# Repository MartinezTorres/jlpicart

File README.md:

# JLPiCart - MSX Cartridge Based on RP2350B

JLPiCart is an experimental MSX cartridge design based on the RP2350B. This is a preliminary version with several known bugs, but early tests show promising results. We have ordered a small production run, and we are offering units to those interested in developing their own RP2350B firmware. If you'd like to obtain one, please contact me.

## Status
The firmware for the PCB is a work in progress. Some features are already functional, while others are still under development. Below is the current status of the key components:

| Feature              | Status                                        |
|----------------------|----------------------------------------------|
| RP2350B main CPU    | Hardware works and tested. Functional.       |
| Primary MSX slot    | Hardware works, code is there, works.        |
| Subslots            | Hardware works, code is there. Not working.  |
| VGA output          | Hardware works, code is there. Almost stable.|
| CRT output          | Hardware works, code is there. Almost stable.|
| TMS9918 emulation   | Hardware works, mode 2 support only. Almost stable. |
| WIFI and BT         | Communication with ESP32 achieved.           |
| E-INK interface     | Not tested.                                  |
| OLED screen         | Hardware works. Bitbanged I2C works.         |
| USB                 | Hardware works. Software is in early stages of development. |
| Battery overcharging| Still investigating hardware.                |

## Schematics and Images
Below are various images related to the JLPiCart hardware design:

### Schematic

### Top Assembly Drawing

### PCB Images
#### Front

#### Back

## Development
We are actively working on improving the firmware. Contributions and feedback are welcome. If you encounter any issues or have suggestions, feel free to reach out.

## Contact
For inquiries, development collaboration, or to request a unit, please contact me.

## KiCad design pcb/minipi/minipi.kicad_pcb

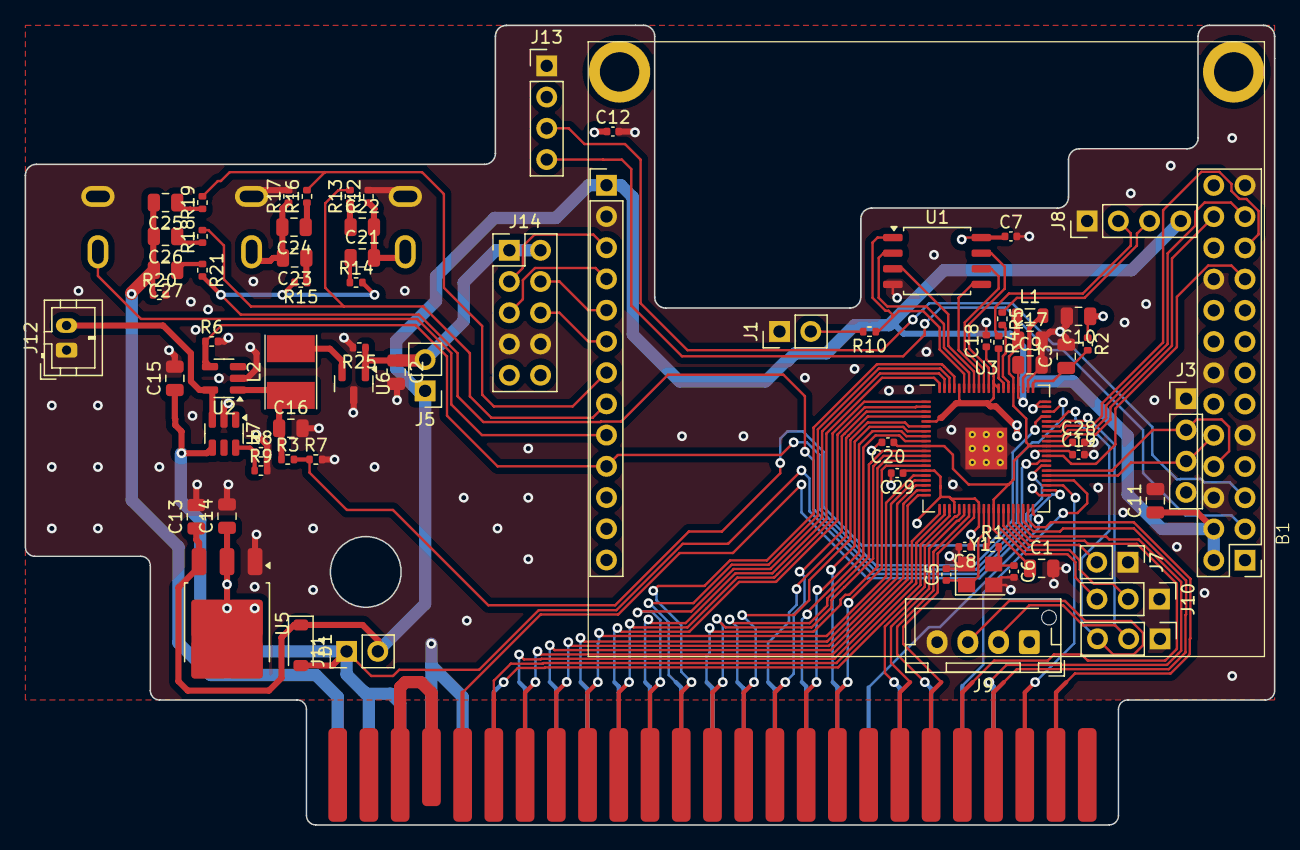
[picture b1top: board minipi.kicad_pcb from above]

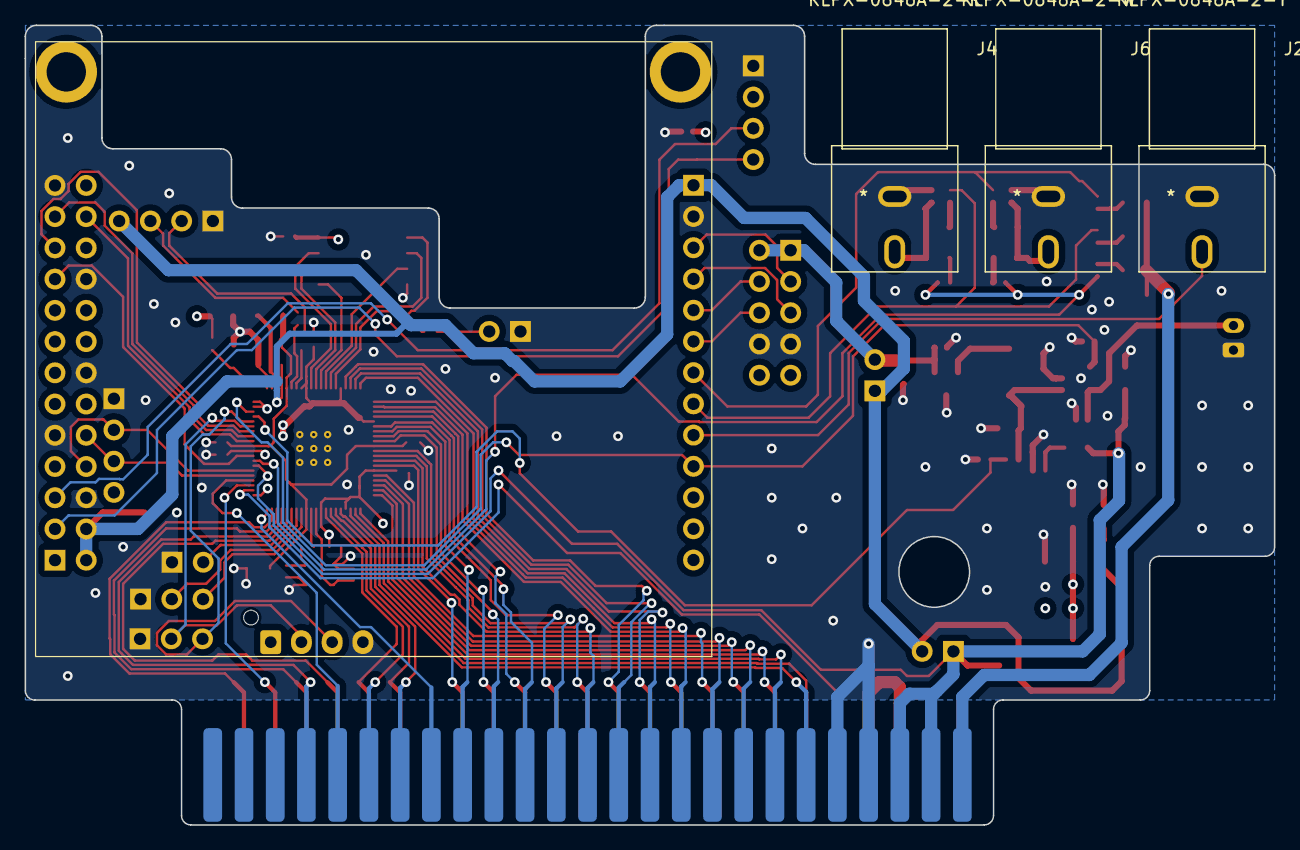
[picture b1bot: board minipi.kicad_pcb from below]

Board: 4 copper layers, 101.6 x 65.0 mm, 75 parts (3 on the bottom side), 96 nets.

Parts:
B1: Orange_PI_Zero_3; Orange Pi Zero 3
BUS1: MSX_SLOT_EDGE-CON; msx_cartridge_basic
C1, C2, C3, C9, C10, C11, C13, C14, C15, C16, C17, C21, C22, C23, C24, C25, C26, C27: 10u; C_0805_2012Metric
C5, C6: 15p; C_0402_1005Metric
C7, C8, C12, C18, C19, C20, C28, C29: 100nF; C_0402_1005Metric
D1: MBR0520; D_SOD-123
J1, J5, J7, J11: Conn_01x02; PinHeader_1x02_P2.54mm_Vertical
J2: KLPX-0848A-2-Y; KLPX-0848A-2-R
J3, J8, J13: Conn_01x04; PinHeader_1x04_P2.54mm_Vertical
J4: KLPX-0848A-2-R
J6: KLPX-0848A-2-W; KLPX-0848A-2-R
J9: Conn_01x04; JST_XH_B4B-XH-AM_1x04_P2.50mm_Vertical
J10: Conn_01x03; PinHeader_1x03_P2.54mm_Vertical
J12: Conn_01x02; JST_PH_B2B-PH-K_1x02_P2.00mm_Vertical
J14: Conn_02x05_Odd_Even; PinHeader_2x05_P2.54mm_Vertical
L1: 3.3u; L_0805_2012Metric
L2: 3.3u; L_Taiyo-Yuden_NR-40xx_HandSoldering
R1, R10: 1k; R_0402_1005Metric
R2, R4, R5: 27; R_0402_1005Metric
R3, R6, R7, R8, R9, R12, R13, R14, R15, R16, R17, R18, R19, R20, R21, R25: 10k; R_0402_1005Metric
U1: W25Q128JVS; SOIC-8_5.23x5.23mm_P1.27mm
U2: AP22804AW5; SOT-23-5
U3: RP2350_80QFN; RP2350-QFN-80-1EP_10x10_P0.4mm_EP3.4x3.4mm_ThermalVias
U5: AMS1117CD-3.3; TO-252-3_TabPin2
U6: TPS613222ADBZ; SOT-23
U7: TP4057; TSOT-23-6
Y1: ABM8-272-T3; Crystal_SMD_3225-4Pin_3.2x2.5mm

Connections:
1V1: C1.1, C17.1, C20.1, C28.1, L1.1, U3.10 (DVDD), U3.32 (DVDD), U3.51 (DVDD), U3.65 (VREG_FB)
3V3: B1.1 (VCC-3V3), B1.17 (VCC-3V3), C7.1, C8.1, C10.1, C12.1, C14.1, C18.1, C19.1, C29.1, J3.4, J13.2, R2.1, U1.8 (VCC), U3.5 (IOVDD), U3.15 (IOVDD), U3.24 (IOVDD), U3.29 (IOVDD), U3.41 (IOVDD), U3.50 (IOVDD), U3.59 (ADC_AVDD), U3.60 (IOVDD), U3.68 (USB_OTP_VDD), U3.69 (QSPI_IOVDD), U3.76 (IOVDD), U5.2 (VO)
5V: B1.2 (VCC-5V), B1.4 (VCC-5V), B1.E1 (VCC-5V), C9.1, C11.1, C13.1, D1.1 (K), J5.1, J8.4, J11.2, U3.64 (VREG_VIN), U5.3 (VI)
5V_BAT: C2.1, J5.2, J14.1, J14.2, R25.1, U6.1 (VOUT)
5V_IN: BUS1.45 (+5V), BUS1.47 (+5V), C15.1, D1.2 (A), J11.1, U3.47 (GPIO38), U7.4 (V_{CC})
/A0: BUS1.28 (A0), U3.77 (GPIO0)
/A1: BUS1.27 (A1), U3.78 (GPIO1)
/A2: BUS1.30 (A2), U3.79 (GPIO2)
/A3: BUS1.29 (A3), U3.80 (GPIO3)
/A4: BUS1.32 (A4), U3.1 (GPIO4)
/A5: BUS1.31 (A5), U3.2 (GPIO5)
/A6: BUS1.22 (A6), U3.3 (GPIO6)
/A7: BUS1.21 (A7), U3.4 (GPIO7)
/A8: BUS1.24 (A8), U3.6 (GPIO8)
/A9: BUS1.17 (A9), U3.7 (GPIO9)
/A10: BUS1.20 (A10), U3.8 (GPIO10)
/A11: BUS1.19 (A11), U3.9 (GPIO11)
/A12: BUS1.23 (A12), U3.11 (GPIO12)
/A13: BUS1.26 (A13), U3.12 (GPIO13)
/A14: BUS1.25 (A14), U3.13 (GPIO14)
/A15: BUS1.18 (A15), U3.14 (GPIO15)
/D0: BUS1.34 (D0), U3.16 (GPIO16)
/D1: BUS1.33 (D1), U3.17 (GPIO17)
/D2: BUS1.36 (D2~), U3.18 (GPIO18)
/D3: BUS1.35 (D3), U3.19 (GPIO19)
/D4: BUS1.38 (D4), U3.20 (GPIO20)
/D5: BUS1.37 (D5), U3.21 (GPIO21)
/D6: BUS1.40 (D6), U3.22 (GPIO22)
/D7: BUS1.39 (D7), U3.23 (GPIO23)
/EN_5V: B1.E10 (PC1), R6.1, U2.4 (EN), U3.58 (GPIO47_ADC7)
/LINEOUT_LL: B1.E7 (LINEOUT-LL), R16.2, R19.2
/LINEOUT_LR: B1.E8 (LINEOUT-LR), R13.2, R18.2
/LINEOUT_RP: R14.2, R15.2, R21.2, U3.48 (GPIO39)
/QSPI_SCLK: U1.6 (CLK), U3.71 (QSPI_SCLK)
/QSPI_SD0: U1.5 (DI(IO0)), U3.72 (QSPI_SD0)
/QSPI_SD1: U1.2 (DO(IO1)), U3.74 (QSPI_SD1)
/QSPI_SD2: U1.3 (IO2), U3.73 (QSPI_SD2)
/QSPI_SD3: U1.7 (IO3), U3.70 (QSPI_SD3)
/QSPI_SS: R10.1, U1.1 (~CS), U3.75 (QSPI_SS)
/RUN: J7.2, U3.35 (RUN)
/SCK: B1.5 (I2C3-SCK), J13.3
/SDA: B1.3 (I2C3-SDA), J13.4
/SND: BUS1.49 (SOUNDOUT), C25.2, C26.2, C27.2, R20.1
/SPI0_CLK: B1.23 (SPI1-CLK), U3.53 (GPIO42_ADC2)
/SPI0_CS: B1.24 (SPI1-CS), U3.52 (GPIO41_ADC1)
/SPI0_MISO: B1.21 (SPI1-MISO), U3.54 (GPIO43_ADC3)
/SPI0_MOSI: B1.19 (SPI1-MOSI), U3.49 (GPIO40_ADC0)
/SW1: BUS1.44 (SW1), BUS1.46 (SW2)
/SWCLK: J10.3, U3.33 (SWCLK)
/SWD: J10.2, U3.34 (SWD)
/SYS_CLK: BUS1.42 (CLOCK), U3.42 (GPIO33)
/TV_OUT: B1.E9 (TV-OUT), J2.1 (In)
/UART0_RP_2_Z: B1.RX, J9.2, U3.55 (GPIO44_ADC4)
/UART0_Z_2_RP: B1.TX, J9.3, U3.56 (GPIO45_ADC5)
/UART1_RP_2_Z: B1.10 (UART5-RX), J3.3, U3.45 (GPIO36)
/UART1_Z_2_RP: B1.8 (UART5-TX), J3.2, U3.46 (GPIO37)
/USB2_DM: B1.E3 (USB2-DM), J14.3
/USB2_DP: B1.E4 (USB2-DP), J14.5
/USB3_DM: B1.E5 (USB3-DM), J14.4
/USB3_DP: B1.E6 (USB3-DP), J14.6
/USB_D+: J8.2, R4.1
/USB_D-: J8.3, R5.1
/V_LIPO_HALF: R3.2, R7.1, U3.57 (GPIO46_ADC6)
/~BUSDIR: BUS1.10 (~BUSDIR), U3.36 (GPIO28)
/~INT: BUS1.8 (~INT), U3.38 (GPIO30)
/~IORQ: BUS1.11 (~IORQ), U3.27 (GPIO26)
/~M1: BUS1.9 (~M1), U3.44 (GPIO35)
/~MERQ: BUS1.12 (~MERQ), U3.28 (GPIO27)
/~RD: BUS1.14 (~RD), U3.26 (GPIO25)
/~RESET: BUS1.15 (~RESET), U3.40 (GPIO32)
/~RFSH: BUS1.6 (~RFSH), U3.43 (GPIO34)
/~SLTSL: BUS1.4 (~SLTSL), U3.39 (GPIO31)
/~USB_BOOT: J1.2, R10.2
/~WAIT: BUS1.7 (~WAIT), U3.37 (GPIO29)
/~WR: BUS1.13 (~WR), U3.25 (GPIO24)
AVDD_3V3: C3.1, R2.2, U3.61 (VREG_AVDD)
GND: B1.6 (GND), B1.9 (GND), B1.14 (GND), B1.20 (GND), B1.25 (GND), B1.E2 (GND), B1.GND, BUS1.41 (GND), BUS1.43 (GND), C1.2, C2.2, C3.2, C5.2, C6.2, C7.2, C8.2, C9.2, C10.2, C11.2, C12.2, C13.2, C14.2, C15.2, C16.2, C17.2, C18.2, C19.2, C20.2, C28.2, C29.2, J1.1, J2.2 (Ext), J3.1, J4.2 (Ext), J6.2 (Ext), J7.1, J8.1, J9.4, J10.1, J12.1, J13.1, J14.7, J14.8, R6.2, R7.2, R8.2, R9.2, R12.2, R17.2, R20.2, R25.2, U1.4 (GND), U2.2 (GND), U3.62 (VREG_PGND), U3.81 (GND), U5.1 (GND), U6.3 (GND), U7.2 (GND), Y1.2, Y1.4
unnamed: C6.1, R1.2, Y1.3
unnamed: C21.1, R14.1
unnamed: C22.1, R13.1
unnamed: C23.1, R15.1
unnamed: C24.1, R16.1
unnamed: C25.1, R19.1
unnamed: C26.1, R18.1
unnamed: C27.1, R21.1
unnamed: C21.2, C22.2, J4.1 (In), R12.1
unnamed: C23.2, C24.2, J6.1 (In), R17.1
unnamed: C16.1, L2.1, R3.1, U2.1 (OUT)
unnamed: R5.2, U3.66 (USB_DM)
unnamed: R4.2, U3.67 (USB_DP)
unnamed: L1.2, U3.63 (VREG_LX)
unnamed: C5.1, U3.30 (XIN), Y1.1
unnamed: R1.1, U3.31 (XOUT)
unnamed: L2.2, U6.2 (SW)
unnamed: R8.1, R9.1, U7.6 (PROG)
V_LIPO: J12.2, U2.5 (IN), U7.3 (BAT)

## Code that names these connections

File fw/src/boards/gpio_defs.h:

#pragma once
// gpio_defs.h — GPIO pin and bit constants for jlpicart_board (RP2350B).
//
// Describes the physical wiring between the RP2350B and the MSX cartridge slot.
// No SDK includes — pure constants safe to use in host tests and bus.cc alike.

#include <cstdint>

// GPIO number → RP2350 GPIO index (0-based).
enum PinMapping : int {
    GPIO_A0  = 0,  GPIO_A1  = 1,  GPIO_A2  = 2,  GPIO_A3  = 3,
    GPIO_A4  = 4,  GPIO_A5  = 5,  GPIO_A6  = 6,  GPIO_A7  = 7,
    GPIO_A8  = 8,  GPIO_A9  = 9,  GPIO_A10 = 10, GPIO_A11 = 11,
    GPIO_A12 = 12, GPIO_A13 = 13, GPIO_A14 = 14, GPIO_A15 = 15,

    GPIO_D0     = 16, GPIO_D1 = 17, GPIO_D2 = 18, GPIO_D3 = 19,
    GPIO_D4     = 20, GPIO_D5 = 21, GPIO_D6 = 22, GPIO_D7 = 23,

    GPIO_WR     = 24,
    GPIO_IORQ   = 25,
    GPIO_MERQ   = 26,
    GPIO_RD     = 27,
    GPIO_BUSDIR = 28,
    GPIO_INT    = 29,
    GPIO_WAIT   = 30,
    GPIO_SLTSL  = 31,

    // GPIOs 32-47 — accessed via sio_hw->gpio_hi_in / gpio_hi_out on RP2350.
    GPIO64_CLK     = 32,
    GPIO64_SND     = 33,
    GPIO64_RESET   = 34,
    GPIO64_M1      = 35,
    GPIO64_RFSH    = 36,
    GPIO64_OLEDSDA = 37,
    GPIO64_OLEDSCK = 38,
    GPIO64_V_VSYNC = 39,
    GPIO64_V_HSYNC = 40,
    GPIO64_V_BLUE  = 41,
    GPIO64_V_GREEN = 42,
    GPIO64_V_RED   = 43,
    GPIO64_UART_TX = 44,
    GPIO64_UART_RX = 45,
    GPIO64_VUSB_EN = 46,
    GPIO64_BATSENS = 47,
};

// Single 32-bit bitmask for GPIOs 0–31 (sio_hw->gpio_in / gpio_out / gpio_oe).
enum PinBitMapping : uint32_t {
    BIT_A0  = 1U << 0,  BIT_A1  = 1U << 1,  BIT_A2  = 1U << 2,  BIT_A3  = 1U << 3,
    BIT_A4  = 1U << 4,  BIT_A5  = 1U << 5,  BIT_A6  = 1U << 6,  BIT_A7  = 1U << 7,
    BIT_A8  = 1U << 8,  BIT_A9  = 1U << 9,  BIT_A10 = 1U << 10, BIT_A11 = 1U << 11,
    BIT_A12 = 1U << 12, BIT_A13 = 1U << 13, BIT_A14 = 1U << 14, BIT_A15 = 1U << 15,

    BIT_D0     = 1U << 16, BIT_D1 = 1U << 17, BIT_D2 = 1U << 18, BIT_D3 = 1U << 19,
    BIT_D4     = 1U << 20, BIT_D5 = 1U << 21, BIT_D6 = 1U << 22, BIT_D7 = 1U << 23,

    BIT_WR     = 1U << 24,
    BIT_IORQ   = 1U << 25,
    BIT_MERQ   = 1U << 26,
    BIT_RD     = 1U << 27,
    BIT_BUSDIR = 1U << 28,
    BIT_INT    = 1U << 29,
    BIT_WAIT   = 1U << 30,
    BIT_SLTSL  = 1U << 31,
};

// High-word bitmask for GPIOs 32–63 (sio_hw->gpio_hi_in on RP2350).
// BIT64_X_HI is bit (GPIO64_X - 32) of the high register.
enum PinBitMappingHi : uint32_t {
    BIT64_CLK_HI     = 1U << (GPIO64_CLK     - 32),  // bit 0
    BIT64_SND_HI     = 1U << (GPIO64_SND     - 32),  // bit 1
    BIT64_RESET_HI   = 1U << (GPIO64_RESET   - 32),  // bit 2
    BIT64_M1_HI      = 1U << (GPIO64_M1      - 32),  // bit 3
    BIT64_RFSH_HI    = 1U << (GPIO64_RFSH    - 32),  // bit 4
    BIT64_OLEDSDA_HI = 1U << (GPIO64_OLEDSDA - 32),  // bit 5
    BIT64_OLEDSCK_HI = 1U << (GPIO64_OLEDSCK - 32),  // bit 6
};

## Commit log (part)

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2024-09-15 firsts tests with pio
2025-02-11 Vga works
2025-03-03 lots of changes
2025-03-04 mini demo for nijmegen
2025-03-21 half-way rework, adding serialization
2025-12-01 huge mess...
2026-03-03 expand and restructure requirements document
    - Add section 3: Use Cases with nine named scenarios
    - Restructure section 5 (System Architecture) and section 6 (Requirements)
    - Split device emulation into ROM Payload Properties, Peripheral Devices,
    and remove SymbOS to Use Cases as a named compatibility target
    - Add Runtime Behavior as its own section, separate from Menu
    - Clean Menu section to focus only on the menu itself
2026-03-05 gitignore esp32-at.bin (large binary, not tracked)
2026-03-08 rename spec_v22.md → spec.md, bootstrapping_v8.md → bootstrapping.md
    Use canonical names as specified in Appendix B of the spec.
2026-03-09 stage 2: add fetch_sdcc step to CI build job
2026-03-09 complete stage 3 test coverage per bootstrapping checklist
    Add missing test cases listed in bootstrapping.md §3.6 and §3.10:
    §3.6 Policy verification:
    - test_policy_verify_sealed_one_bit_mutation_fails: flip one bit in flags,
    HMAC must reject it
    - test_policy_verify_sealed_wrong_key_fails: HMAC computed with a different
    key is rejected even if structurally valid
2026-03-09 stage 4: fix ring_push_msg wrap+full bug and clean up smells
    ring_push_msg free-space check was wrong when wrapping is needed.
    When frame_len > to_end, the [head, size) bytes are permanently wasted
    by the wrap marker; space consumed = to_end + frame_len, not frame_len.
    With ring_size=512 and max_frame=256 this was reachable: e.g. head=300,
    tail=4, frame_len=256 would pass the old check and overwrite unread
    consumer data at positions [4, 255]. Fixed by computing:
2026-03-09 stage 5: fix three spec compliance bugs in Z80 menu stub
    1. Joystick encoding inverted (MUST violation, spec §8 InputSnapshot):
    joy1/joy2 bits are active-low (0=pressed, 1=released) per spec, matching
    kbd_rows convention. Previous code started at 0 and set bits when active
    (active-high). Fixed: start at 0xFF (all released), clear bits on press.
    Trigger logic was also inverted (tested trig == 0 instead of trig != 0).
    2. PUT_TEXT: no clipping (MUST violation, spec §8):
2026-03-09 stage 6: fix bugs and clean up from deep analysis
    - Add STORAGE_NOT_FOUND (0x0303) DiagCode; use it in KvStore::get()
    instead of STORAGE_CORRUPT, which had the wrong semantics
    - Fix KvStore::init() tombstone logic: skip slot allocation entirely
    when a tombstone is encountered for a key not in the index
    - Parameterise storage_check_health() with explicit kv/log offsets
    instead of hardcoding flash layout constants; this makes it testable
2026-03-10 stage 7: Collections v1 — manifest, install engine, receipts, host tests
    Add the collection format, JSON manifest parser, atomic USB install engine,
    and install receipt logging. All 16 host tests pass (11/11 test targets).
    - src/content/collection_format.h: CollectionRecord (357B packed), bundle
    file constants, KV key/state constants, BundleSigEnvelope
    - src/content/manifest.h: CollectionManifest + PayloadEntry structs
    - src/content/manifest_parser.{h,cc}: minimal recursive-descent JSON parser
2026-03-10 stage 7: second audit — append_log guard, scan_records refactor, doc fixes
    - append_log: reject ALOG_TYPE_ERASED (0xFF) in append() — writing the
    end-of-log sentinel type would silently truncate the log on the next
    init() scan
    - append_log: extract scan_records() private helper; init() and iterate()
    were duplicating ~35 lines of identical partition-walking logic
    - kv_store.h: correct stale get() doc comment (now accurately describes
2026-03-11 stage 8: audit — fix include placement, static assert, clean test comments
    - capability_registry.h: move #include "allocator/resource_model.h" to
    the top with the other includes (was placed after the block comment)
    - spine/activation.h: add static_assert(CAP_ID_MAX == PAYLOAD_CAP_ID_MAX)
    so a divergence between the two constants fires at compile time rather
    than silently corrupting capability id strings
    - test_allocator.cc: remove dead `struct BlockGammaPolicy {}` declaration;
2026-03-12 stage 10: audit — fix log message, doc errors, code quality
    - main.cc: split the else-branch into two distinct log messages so
    load_default_payload() failure is distinguished from data_size==0
    - content_store.h: fix load_collection/load_default_payload doc comments;
    both functions do not check col.state — callers must call
    has_active_collection() first if that distinction matters
    - installer.cc: hoist KV_PAYLOAD_PREFIX length as a static constexpr
2026-03-15 stage 12: fix build_openmsx.sh GLEW bootstrap sequencing, pin openMSX data dir
    - build_openmsx.sh: add required-header guard (SDL2, png); add no-sudo GLEW
    bootstrap via apt-get download + dpkg -x; delete components_defs.mk after
    patching probed_defs.mk so the full build regenerates it with GLEW enabled
    - run_test.sh: remove system openMSX fallback (pinned build required); default
    OPENMSX_SYSTEM_DATA to third_party/openMSX/share to avoid version mismatch
    with system Tcl scripts
2026-03-15 stage 14: USB host — tinyusb MSC + FatFs + UsbInstallScanner
    Wires tinyusb (ext/tinyusb) for USB mass-storage host class so the
    firmware can install Collections from a USB stick at boot.
    New files:
    src/usb/tusb_config.h — tinyusb host config (MSC-only, RP2040 MCU)
    src/usb/usb_host.h/cc — UsbHost: init, poll, mount callbacks
    src/usb/usb_install_reader.h/cc — InstallReader backed by FatFs over MSC
2026-03-16 stage 22: DeviceIdentity — ed25519 DIK, GET_DEVICE_ID, scoped IDs
    Generate or load an ed25519 keypair on first boot (SYSTEM_KV). Sign
    with platform_sign (OpenSSL on host, stub on hardware). GET_DEVICE_ID
    returns a 16-byte HKDF-SHA256 scoped ID keyed to the public key.
    All 24 host tests pass.
2026-03-16 stage 24: hardware ed25519 via Monocypher + pico_rand TRNG
    Wires the RP2350 hardware TRNG (pico_rand / get_rand_64) into
    platform_random_bytes() for DIK seed generation.
    Replaces the hardware ed25519 stub with Monocypher (vendored at
    src/crypto/monocypher/), which is formally verified, BSD-2-Clause /
    CC0, and self-contained. Resolves the mbedTLS 3.6.2 blocker where
    PSA_WANT_ECC_TWISTED_EDWARDS_255 keygen is DEPENDENCY_NOT_IMPLEMENTED_YET.
2026-03-16 stage 27: PSG (AY-3-8910) emulation — audio synthesis, bus wiring, host tests
    Implements full AY-3-8910 / YM2149 software emulation:
    - psg.h / psg.cc: complete register state machine, Q16 fixed-point tone/noise
    generators, 17-bit LFSR noise, uint64_t envelope counter (avoids overflow
    for large EP values), all 16 envelope shapes, logarithmic amplitude table,
    RAMFUNC IO callbacks for ports 0xA0/0xA1/0xA2, PWM audio output on GPIO64_SND
    at ~44100 Hz (hardware), no-op in host builds.
2026-03-16 stage 29: SCC emulation — Konami SCC 5-channel wavetable synthesiser
    - scc.h / scc.cc: SccState, bus callbacks (RAMFUNC), scc_compute_sample(),
    scc_setup(), scc_service(), g_scc_sample shared with psg_service() mixer
    - mappers.h / mappers.cc: mapper_setup_konami_scc() — Konami banking with
    SCC register space at 0x9800–0x9FFF; segment 4 dual-use (bank + SCC)
    - mapping_plan.h / .cc: MapperType::KONAMI_SCC; "konami_scc" string roundtrip
    - CMakeLists.txt (fw + tests): scc.cc added to firmware and test targets;
2026-03-30 stage 31: production blockers — SCC state, reset callback, OPL4 wave ROM, ed25519 sig
    Blocker 1 (SCC state sharing): apply_mapping() previously allocated a static
    local SccState array that was invisible to Core 1's service loop. Move the
    array into PeripheralManager as a member (scc_states_[]) and expose active_scc()
    so main.cc Core 1 loop services the same instance the mapper callbacks write to.
    Blocker 2 (MSX reset callback): Add Cartridge::reset_fn (void(*)(Cartridge&))
    and implement reset functions for every stateful mapper (Konami, Konami-Z,
2026-03-31 stage 32: monotonic uptime timestamp for leaderboard entries
    leader_submit() now writes time_us_64()/1e6 (seconds since boot) into
    LeaderEntry.timestamp on firmware; stays 0 in host tests (no clock).
    This removes the TODO(stage-rtc) stub and gives leaderboard entries a
    meaningful ordering timestamp without requiring a battery-backed RTC.
2026-04-01 stage 32: ESP32 AT transport + Network service (0x02)
    - TransportEspAt: UART0 on GPIO44/45 (115200 baud); AT+CWJAP?/AT+CIFSR
    for WiFi status; AT+HTTPCLIENT for HTTP GET/POST/PUT/DELETE.
    EN and BOOT pins are not wired on the reference board — AT firmware
    must be pre-flashed externally (confirmed in old port stubs).
    HTTPS uses TLS on ESP32 (not RP2350); documented limitation for v1.
    - NetworkService (SVC_NETWORK 0x02): NET_STATUS and NET_HTTP_REQUEST
2026-04-12 stage 32: wire network transport into main.cc boot sequence
    TransportEspAt gains connect(ssid, pass) — issues AT+CWJAP and blocks
    up to ~16 s for association. main.cc reads network_enabled / wifi_ssid
    / wifi_pass from SystemSettings, initialises the transport, calls
    connect() if an SSID is stored, then binds it to the API window so
    the network service feature bit is live on hardware.
2026-04-12 stage 32: OPL3 FM rhythm mode synthesis (gap #4)
    Implements all 5 OPL3 percussion instruments triggered by 0xBD bits [4:0]:
    BD (Bass Drum) bit 4 — op12+op15, standard 2-op FM (ch6 params)
    HH (Hi-Hat) bit 0 — op13, phase noise via rm_xor bit flip
    SD (Snare Drum) bit 3 — op16, phase from HH sign + rm_xor
    TT (Tom-Tom) bit 2 — op14, standard single-op sine
    CY (Cymbal) bit 1 — op17, phase combination with HH bit 8 + rm_xor
2026-05-04 updated documentation
2026-05-08 cleanup data
2026-05-09 move Pico SDK from fw/.pico-sdk to fw/ext/tools/pico-sdk
    Consistent with the third-party consolidation: all toolchain artifacts
    now live under fw/ext/ rather than scattered across the repo.
2026-05-09 move .vscode to repo root and add Pico SDK path for VS Code extension
    Tasks now resolve from repo root. Added settings.json with pico-sdk.paths
    so the VS Code Pico extension finds the SDK alongside the CMakeLists.txt
    definition.
2026-05-09 Remove all git submodules, consolidate into single get_deps.sh
    Replace git submodules (tinyusb, esp-at, openmsx, esp-serial-flasher)
    with tarball downloads managed by a single get_deps.sh script that reads
    lock.yml. All dependencies are now treated uniformly — no distinction
    between submodules and downloaded artifacts.
    - Remove .gitmodules, fetch_pico_sdk.sh, get_sdcc.sh, apply_patches.sh
    - Add get_deps.sh (downloads all deps from lock.yml)
2026-05-09 Move dependency bootstrap files from ext/ to util/
    ext/ now only contains downloaded/derived content and is fully
    gitignored. The bootstrap files (get_deps.sh, lock.yml, patches,
    at.py) move to util/ so ext/ can be wiped without losing the
    scripts that repopulate it.
    Also remove duplicate tinyusb/esp_at entries from lock.yml and
    untrack the downloaded source directories that were accidentally

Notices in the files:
parts and their libraries:
Copyright 2021 Accelerated Designs. All rights reserved.
